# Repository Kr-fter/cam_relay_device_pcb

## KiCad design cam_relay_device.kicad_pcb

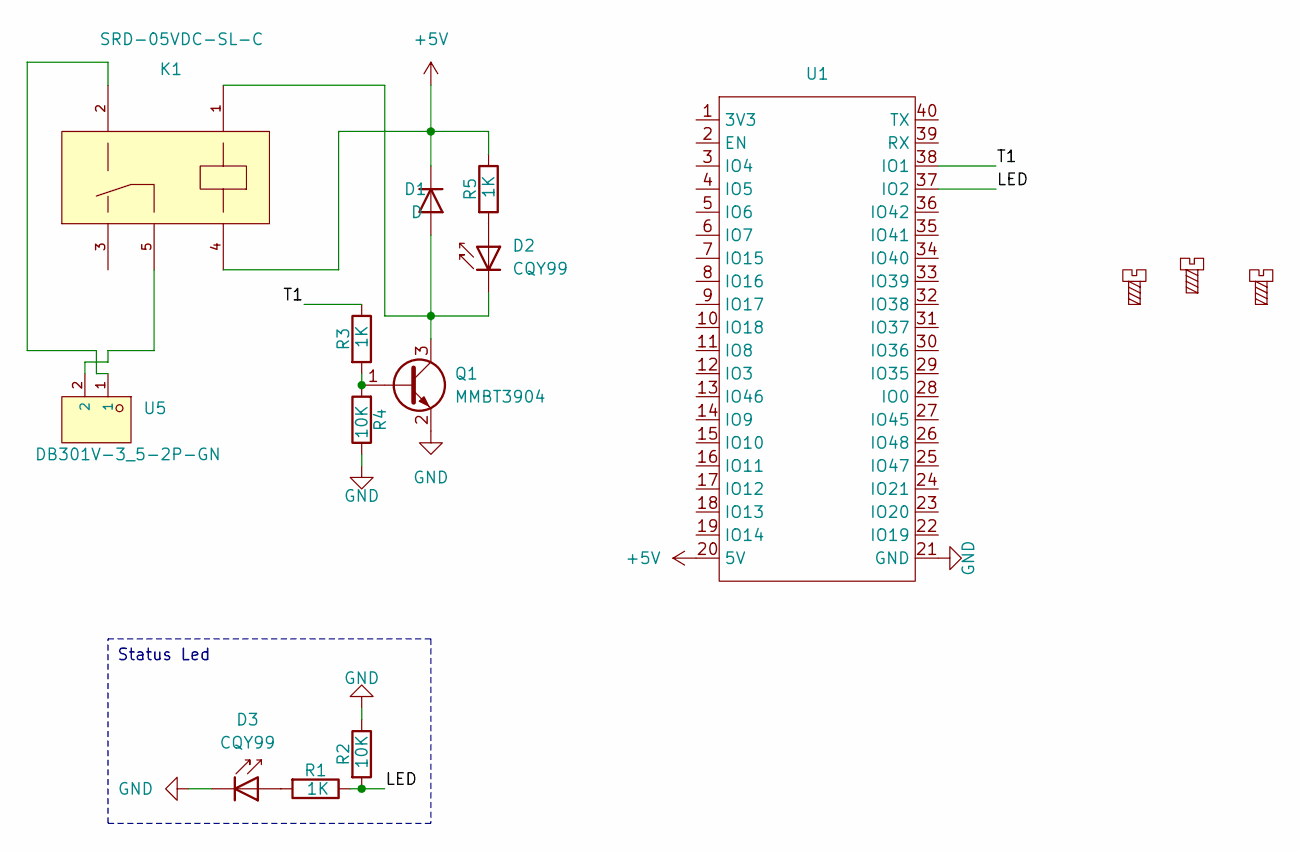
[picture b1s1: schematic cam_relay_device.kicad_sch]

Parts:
D1: D; SOD-123FL_L2.8-W1.8-LS3.7-RD; LCSC C2892681
D2, D3: CQY99; LED_D5.0mm_IRGrey
H1, H2, H3: MountingScrew; MountingHole_2.2mm_M2
K1: SRD-05VDC-SL-C; RELAY-TH_SRD-XXVDC-XL-C; LCSC C35449
Q1: MMBT3904; SOT-23; LCSC C181119
R1, R3, R5: 1K; R0603; LCSC C21190
R2, R4: 10K; R0603; LCSC C25804
U1: esp32-s3-cam-devkit
U5: DB301V-3_5-2P-GN; TerminalBlock_MaiXu_MX126-5.0-02P_1x02_P5.00mm; LCSC C695629

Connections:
+5V: D1.1 (K), K1.4, R5.1, U1.20 (5V)
/LED: R1.1, R2.2, U1.37 (IO2)
/T1: R3.1, U1.38 (IO1)
GND: D3.1 (K), Q1.2 (E), R2.1, R4.1, U1.21 (GND)
unnamed: D1.2 (A), D2.1 (K), K1.1, Q1.3 (C)
unnamed: D2.2 (A), R5.2
unnamed: D3.2 (A), R1.2
unnamed: K1.2, U5.1
unnamed: K1.5, U5.2
unnamed: Q1.1 (B), R3.2, R4.2

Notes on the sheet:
Status Led

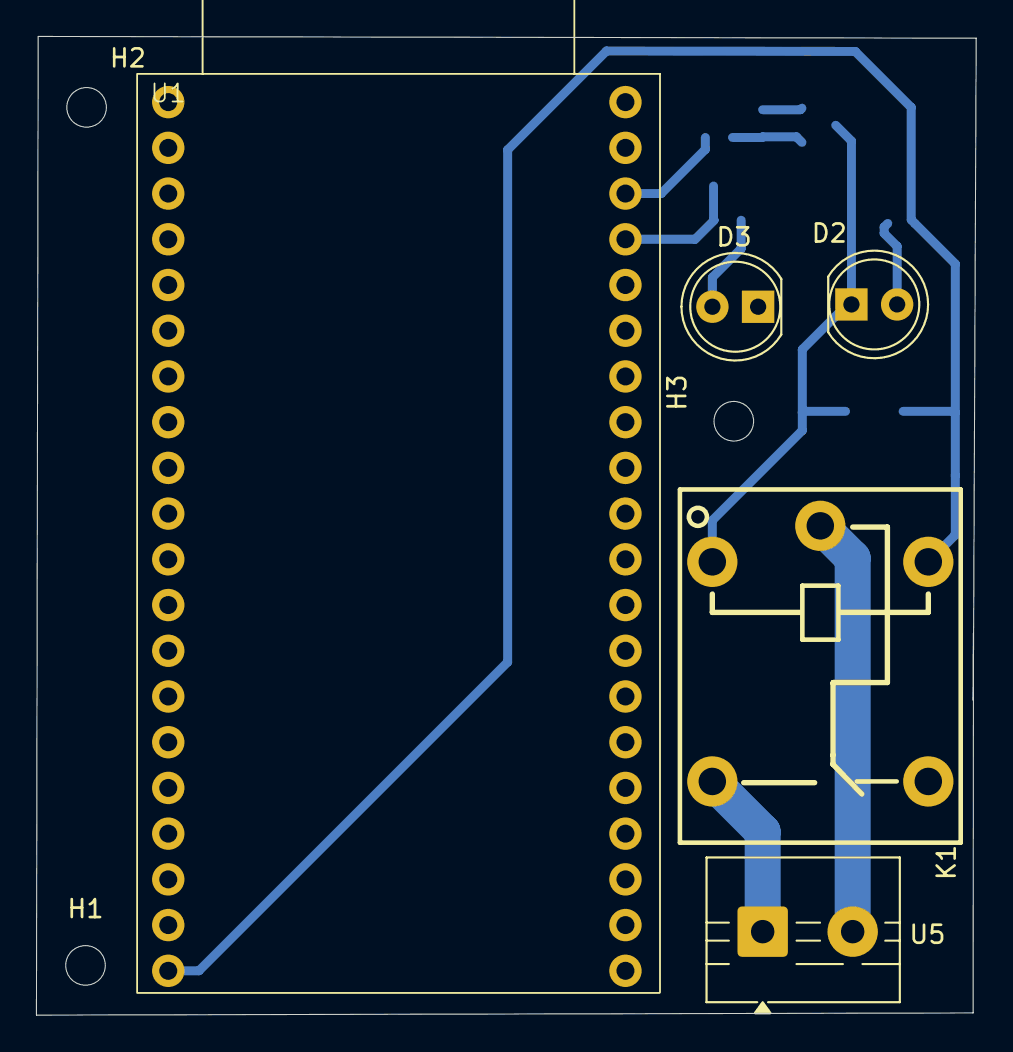
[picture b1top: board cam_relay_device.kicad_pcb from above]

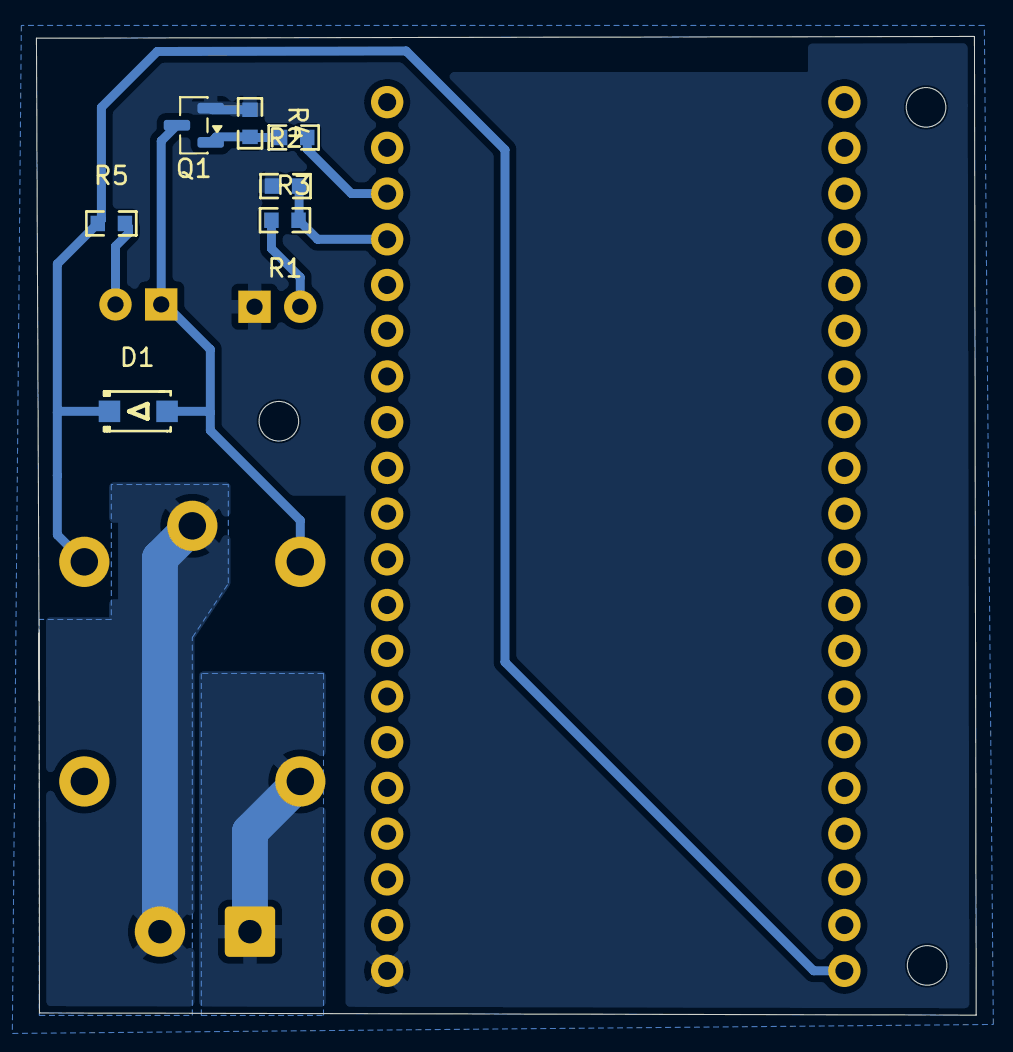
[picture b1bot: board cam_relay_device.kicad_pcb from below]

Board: 2 copper layers, 52.2 x 54.4 mm, 15 parts (7 on the bottom side), 10 nets.

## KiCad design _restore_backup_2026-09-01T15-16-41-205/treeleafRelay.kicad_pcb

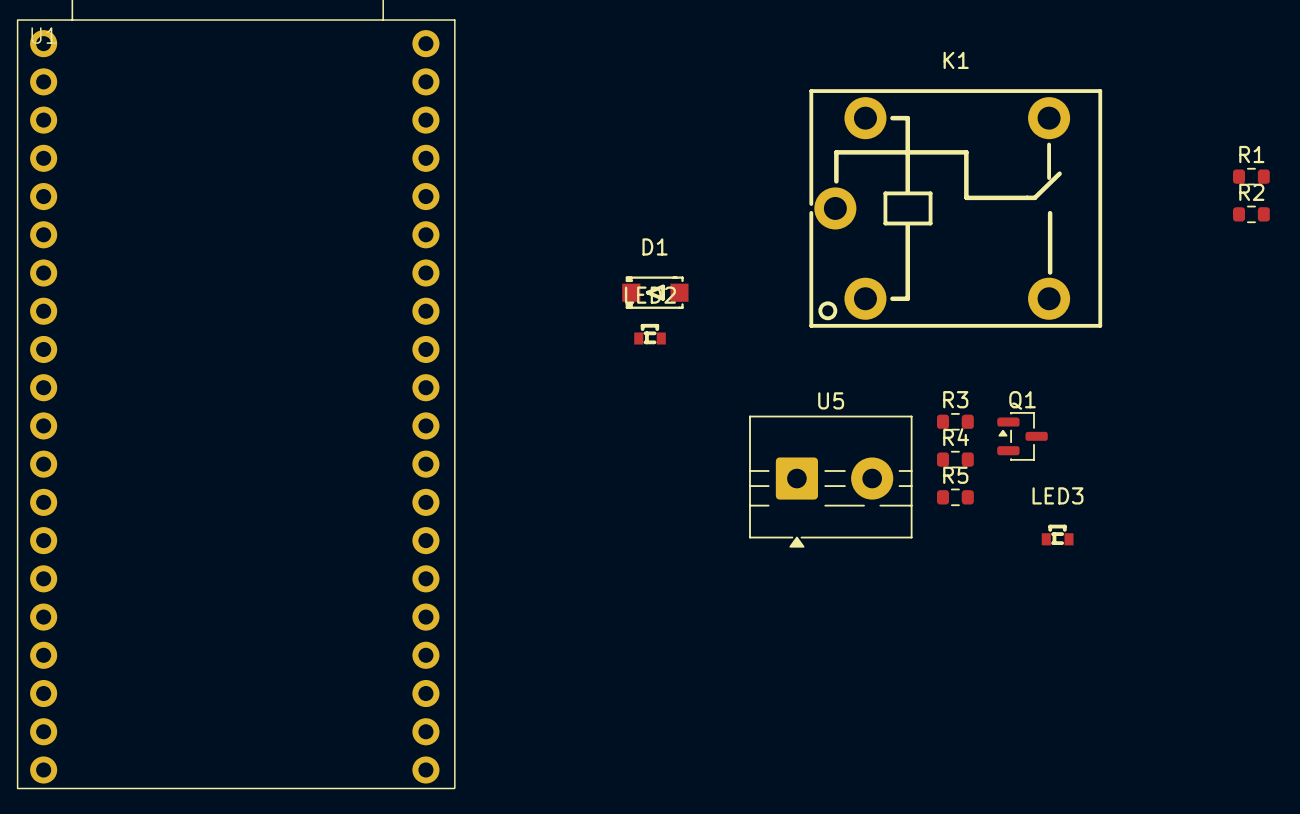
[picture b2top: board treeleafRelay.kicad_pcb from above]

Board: 2 copper layers, 12 parts (0 on the bottom side), 9 nets, no tracks yet.

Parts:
D1: D; SOD-123FL_L2.8-W1.8-LS3.7-RD
K1: SRD-05VDC-SL-C; RELAY-TH_SRD-XXVDC-XL-C
LED2, LED3: XL-1606UGC; LED-SMD_L1.7-W1.1-R-RD_ORANGE
Q1: MMBT3904; SOT-23
R1, R3, R5: 1K; R_0603_1608Metric
R2, R4: 10K; R_0603_1608Metric
U1: esp32-s3-cam-devkit
U5: DB301V-3_5-2P-GN; TerminalBlock_MaiXu_MX126-5.0-02P_1x02_P5.00mm

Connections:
+5V: D1.1 (K), K1.4, R5.1
/LED: R1.1, R2.2
GND: LED3.1 (K), Q1.2 (E), R2.1, R4.1
unnamed: D1.2 (A), K1.1, LED2.1 (K), Q1.3 (C)
unnamed: K1.2, U5.2
unnamed: K1.5, U5.1
unnamed: LED2.2 (A), R5.2
unnamed: LED3.2 (A), R1.2
unnamed: Q1.1 (B), R3.2, R4.2
